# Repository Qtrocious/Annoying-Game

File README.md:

# Annoying Game
A physical annoying game!!

# PCB

# "In life we are alw- " 

This was my first introduction to C++, it was... Interesting.
Nonetheless it was new, it's obviously super different from python, but i'm gonna try in the near future on coding in c++

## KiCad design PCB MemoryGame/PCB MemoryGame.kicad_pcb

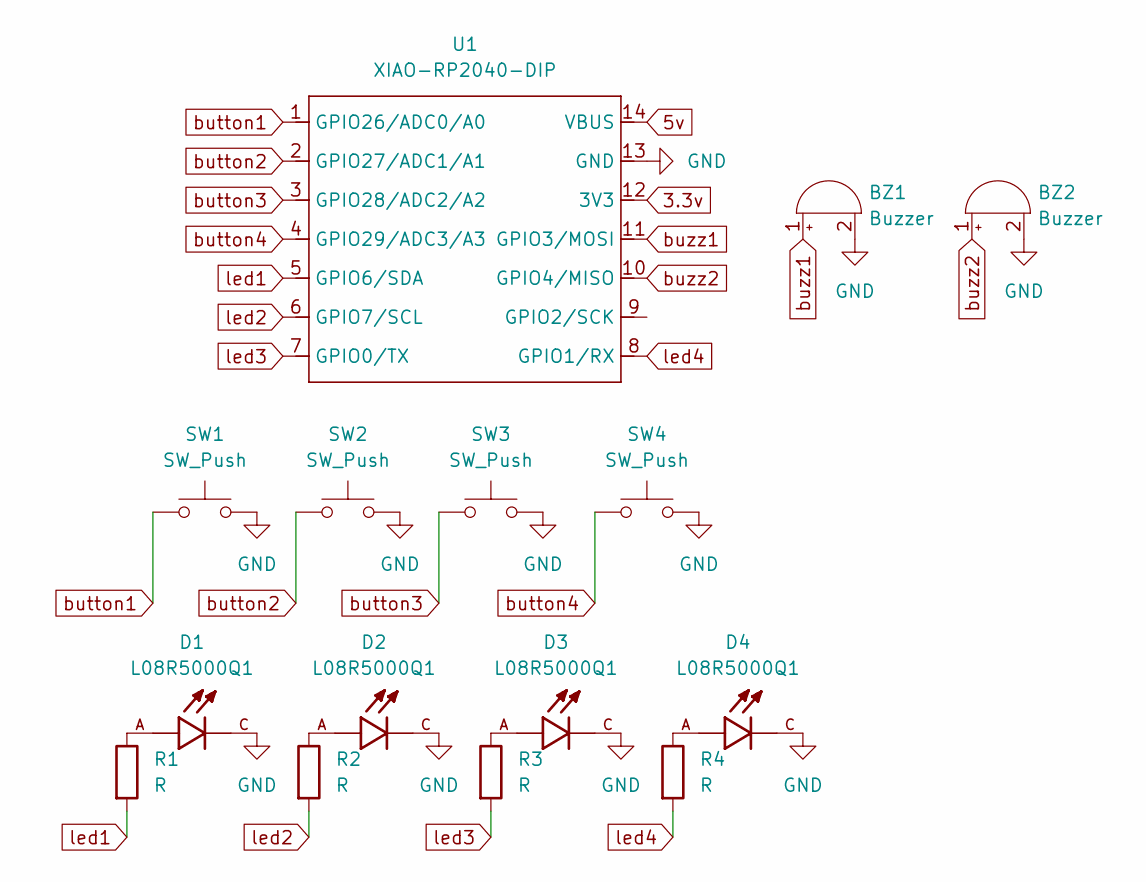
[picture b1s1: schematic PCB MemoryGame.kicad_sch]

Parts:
BZ1, BZ2: Buzzer; Buzzer_12x9.5RM7.6
D1, D2, D3, D4: L08R5000Q1; LEDRD254W57D500H1070; PARTREV NA
R1, R2, R3, R4: R; R_Axial_DIN0204_L3.6mm_D1.6mm_P5.08mm_Horizontal
SW1, SW2, SW3, SW4: SW_Push; SW_Cherry_MX_1.00u_PCB
U1: XIAO-RP2040-DIP

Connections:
3.3v: U1.12 (3V3)
5v: U1.14 (VBUS)
GND: BZ1.2 (-), BZ2.2 (-), D1.C, D2.C, D3.C, D4.C, SW1.2, SW2.2, SW3.2, SW4.2, U1.13 (GND)
unnamed: D1.A, R1.1
unnamed: D2.A, R2.1
unnamed: D3.A, R3.1
unnamed: D4.A, R4.1
button1: SW1.1, U1.1 (GPIO26/ADC0/A0)
button2: SW2.1, U1.2 (GPIO27/ADC1/A1)
button3: SW3.1, U1.3 (GPIO28/ADC2/A2)
button4: SW4.1, U1.4 (GPIO29/ADC3/A3)
buzz1: BZ1.1 (+), U1.11 (GPIO3/MOSI)
buzz2: BZ2.1 (+), U1.10 (GPIO4/MISO)
led1: R1.2, U1.5 (GPIO6/SDA)
led2: R2.2, U1.6 (GPIO7/SCL)
led3: R3.2, U1.7 (GPIO0/TX)
led4: R4.2, U1.8 (GPIO1/RX)

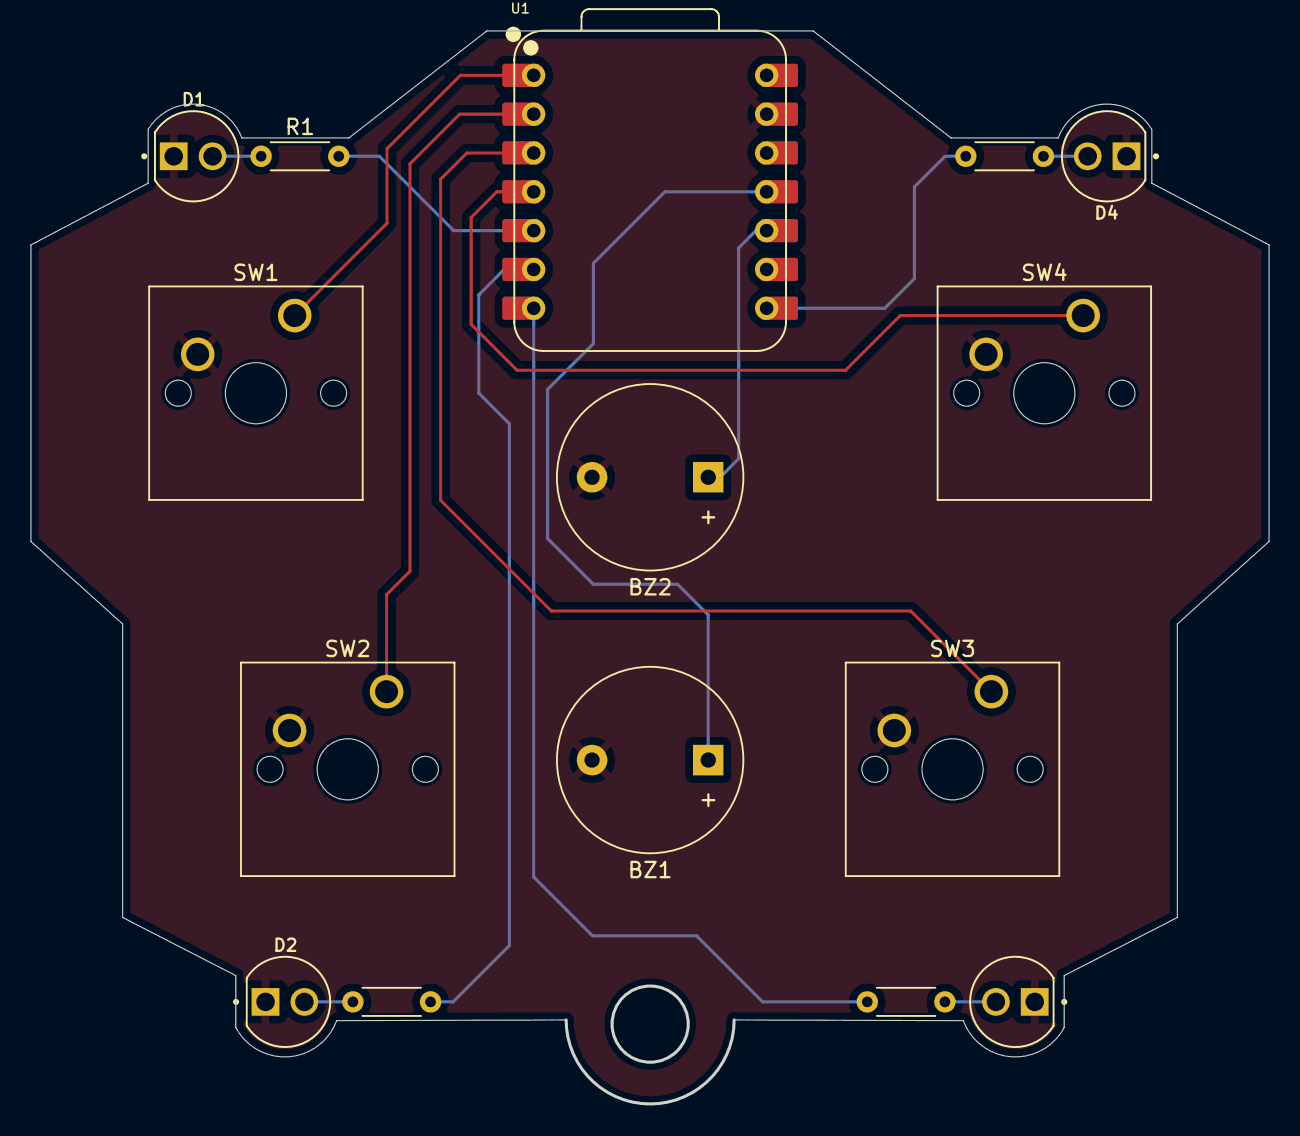
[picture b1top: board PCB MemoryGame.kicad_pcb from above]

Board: 2 copper layers, 80.9 x 70.1 mm, 15 parts (0 on the bottom side), 15 nets.

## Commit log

2025-07-05 all files to repo
